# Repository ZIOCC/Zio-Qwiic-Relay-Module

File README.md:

# Zio Qwiic Relay Module

> This product can be available for purchase [here](https://www.smart-prototyping.com/Zio-Qwiic-Relay).

#### Description

Sometimes we need to control high voltage appliances to work with our components. To control that high current, we send an MCU command to a relay module. There are many relay modules out there that can do just that, but what is so great about ours is, it has I2C feature embedded in the module, hence the name ‘Qwiic Relay Module’.

By adding an I2C gateway MCU (ATTINY85-20SU), we have turned this relay module into Qwiic compatible module, no more complications with jumper wire connections, just connect with Qwiic cable!

> Warning: The max. load of this module is not the relay itself, it is the line that connects the pins on the PC. Our module max. allowed current is 4.5A! For your safety, do not connect to devices that are higher than 4.0A.  

#### Specification

* MCU Operation Voltage: 3.3V
* Max. Load for appliances: 4.0A at 125V AC or 250V AC
* Gateway MCU: ATTINY85-20SU
* I2C address: 0x07- 0x78 (Default:0x18)
* Weight: 17.0G
* Dimension: 27.4 x 55.9 x 17.2 (H) mm

#### Links

* [Eagle File and gerber files](https://github.com/ZIOCC/Zio-Qwiic-Relay-Module)
* [Schematic](https://github.com/ZIOCC/Zio-Qwiic-Relay-Module/blob/master/Zio%20Qwiic%20Relay%20Module%20Schematic%20PDF.pdf)
* [Gateway firmware](https://github.com/ZIOCC/Zio-Qwiic-Relay-Module/tree/master/firmware/Qwiic_Relay_Gateway_Firmware)

> This Qwiic version Relay module is referenced from [Sparkfun's Qwiic Relay](https://www.sparkfun.com/products/14712) design and their firmware.

> The gateway MCU is ATTINY85-20SU, check out the datasheet [here](https://www.mouser.com/datasheet/2/268/Atmel-2586-AVR-8-bit-Microcontroller-ATtiny25-ATti-1315542.pdf).

> ###### About Zio
> Zio is a new line of open sourced, compact, and grid layout boards, fully integrated for Arduino and Qwiic ecosystem. Designed ideally for wearables, robotics, small-space limitations or other on the go projects. Check out other awesome Zio products [here](https://www.smart-prototyping.com/Zio).

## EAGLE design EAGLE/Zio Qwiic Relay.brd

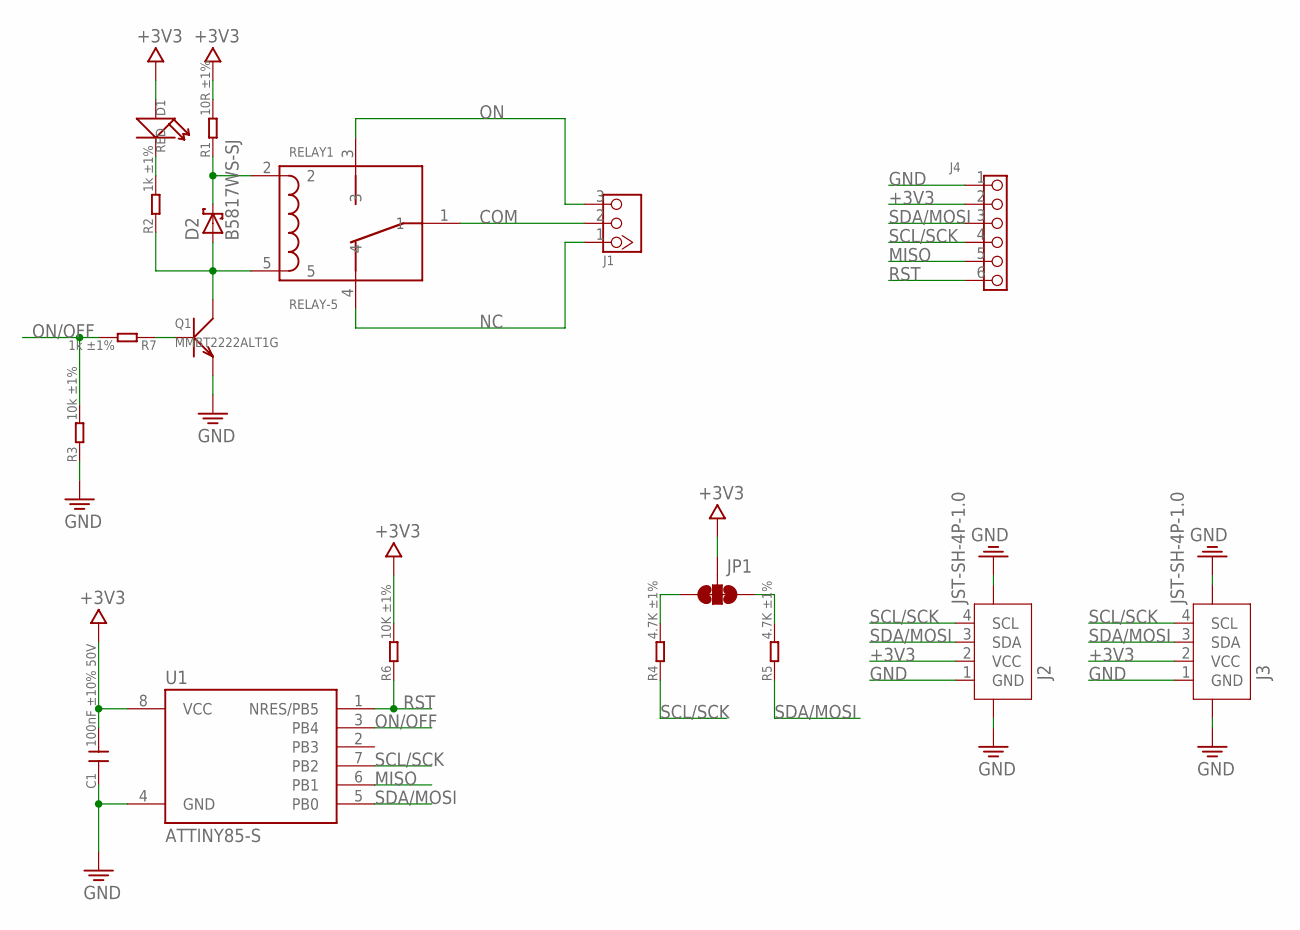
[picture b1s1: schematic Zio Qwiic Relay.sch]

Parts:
C1: 100nF ±10% 50V; C0603
D1: RED; LED-0603
D2: B5817WS-SJ; SOD323
J1: HEADER-3P; 3P-SCREW-5.08
J2, J3: JST-SH-4P-1.0; JST-SH-4P
J4: HEADER-6P-60/35MIL; 6P-2.54-60/35MIL
JP1: SMT-JUMPER_3_2-NC_TRACE
Q1: MMBT2222ALT1G; SOT23
R1: 10R ±1%; R0603
R2, R7: 1k ±1%; R0603
R3: 10k ±1%; R0603
R4, R5: 4.7K ±1%; R0603
R6: 10K ±1%; R0603
RELAY1: RELAY-5
U1: ATTINY85-S; SOIC8_EIAJ_208MIL

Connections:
+3V3: C1.2, D1.+, J2.2 (VCC), J3.2 (VCC), J4.2, JP1.2, R1.2, R6.2, U1.8 (VCC)
COM: J1.2, RELAY1.1
GND: C1.1, J2.1 (GND), J2.NC1 (5), J2.NC2 (6), J3.1 (GND), J3.NC1 (5), J3.NC2 (6), J4.1, Q1.2 (E), R3.1, U1.4 (GND)
MISO: J4.5, U1.6 (PB1)
unnamed: D2.- (C), R1.1, RELAY1.2
unnamed: Q1.1 (B), R7.1
unnamed: D1.-, R2.2
unnamed: D2.+ (A), Q1.3 (C), R2.1, RELAY1.5
unnamed: JP1.3, R4.2
unnamed: JP1.1, R5.2
NC: J1.1, RELAY1.4
ON: J1.3, RELAY1.3
ON/OFF: R3.2, R7.2, U1.3 (PB4)
RST: J4.6, R6.1, U1.1 (NRES/PB5)
SCL/SCK: J2.4 (SCL), J3.4 (SCL), J4.4, R4.1, U1.7 (PB2)
SDA/MOSI: J2.3 (SDA), J3.3 (SDA), J4.3, R5.1, U1.5 (PB0)

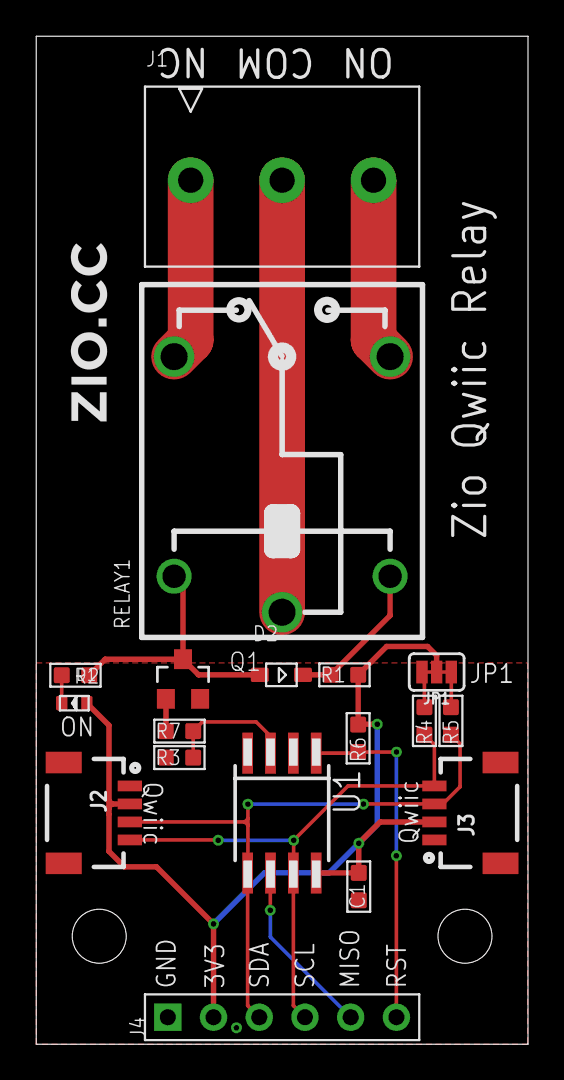
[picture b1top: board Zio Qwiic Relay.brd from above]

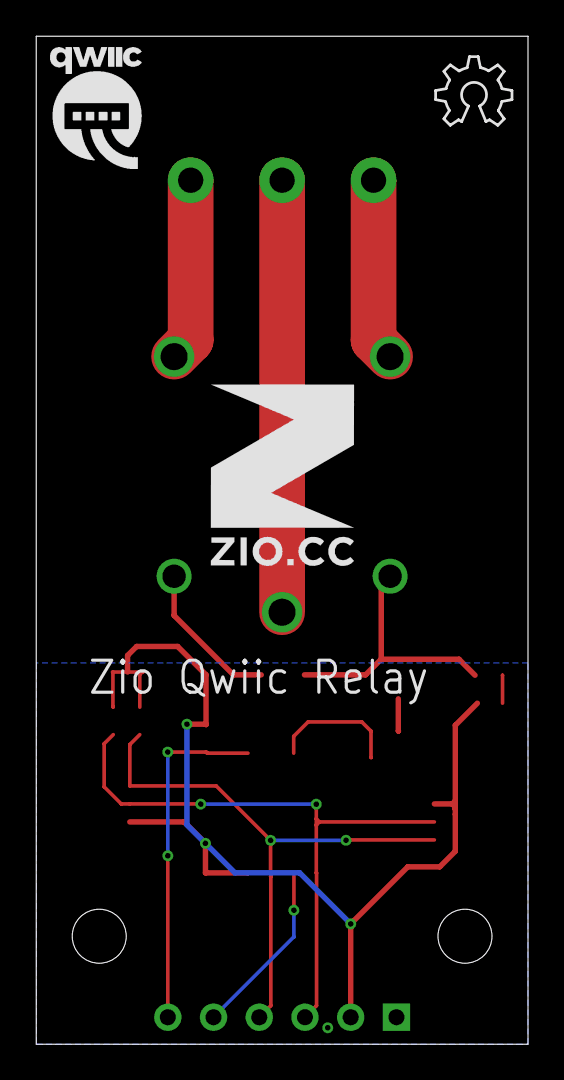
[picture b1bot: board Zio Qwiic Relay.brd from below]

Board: 2 copper layers, 27.3 x 56.0 mm, 22 parts (3 on the bottom side), 16 nets.

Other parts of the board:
U$3: 10MM
U$6: QWIIC-LOGO-MEDIUM
U$7: OSHW_6X150_NOTEXT
U$9: 2MM

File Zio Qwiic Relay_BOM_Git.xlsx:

| BOM quantity |  |  | Zio Qwiic Relay | V 1.0 |  |  |  |  | Harry | 2018.8.31
 | Part Identification |  |  |  |  |  |  |  | Customer Information |  | Quantity
# | Part ID / Reference | Manufacturer | Part / Order Number | Description | Value | Package | THT (y/n) | Pins / Pads | Source/Link/ Datasheet/Note | Source / Target Price | Quantity per BOM
1 | C1 |  |  |  | 100nF ±10% 50V | C0603 | n | 2 |  |  | 1
2 | D1 |  |  |  | RED | LED-0603 | n | 2 |  |  | 1
3 | D2 | MDD | B5817WS-SJ |  | B5817WS-SJ | SOD323 | n | 3 |  |  | 1
4 | J1 | KANGNEX | WJ301V-5.0-3P |  | WJ301V-5.0-3P | 3P-SCREW-5.08 | y | 3 |  |  | 1
5 | J2, J3 |  |  |  | JST-SH-4P-1.0 | JST-SH-4P | n | 6 |  |  | 2
6 | J4 |  | NA |  | 6P-2.54 | 6P-2.54-60/35MIL | y | 6 |  |  | 1
7 | Q1 | ON | MMBT2222ALT1G |  | MMBT2222ALT1G | SOT23 | n | 3 |  |  | 1
8 | R1 |  |  |  | 10R ±1% | R0603 | n | 2 |  |  | 1
9 | R2, R7 |  |  |  | 1k ±1% | R0603 | n | 2 |  |  | 2
10 | R3, R6 |  |  |  | 10k ±1% | R0603 | n | 2 |  |  | 2
11 | R4, R5 |  |  |  | 4.7K ±1% | R0603 | n | 2 |  |  | 2
12 | RELAY1 | 松乐 | SRD-03VDC-SL-C 蓝色 |  | RELAY-5 | RELAY-5 | y | 5 |  |  | 1
13 | U1 | MICROCHIP | ATTINY85-20SU |  | ATTINY85-S | SOIC8_EIAJ_208MIL | n | 8 |  |  | 1
